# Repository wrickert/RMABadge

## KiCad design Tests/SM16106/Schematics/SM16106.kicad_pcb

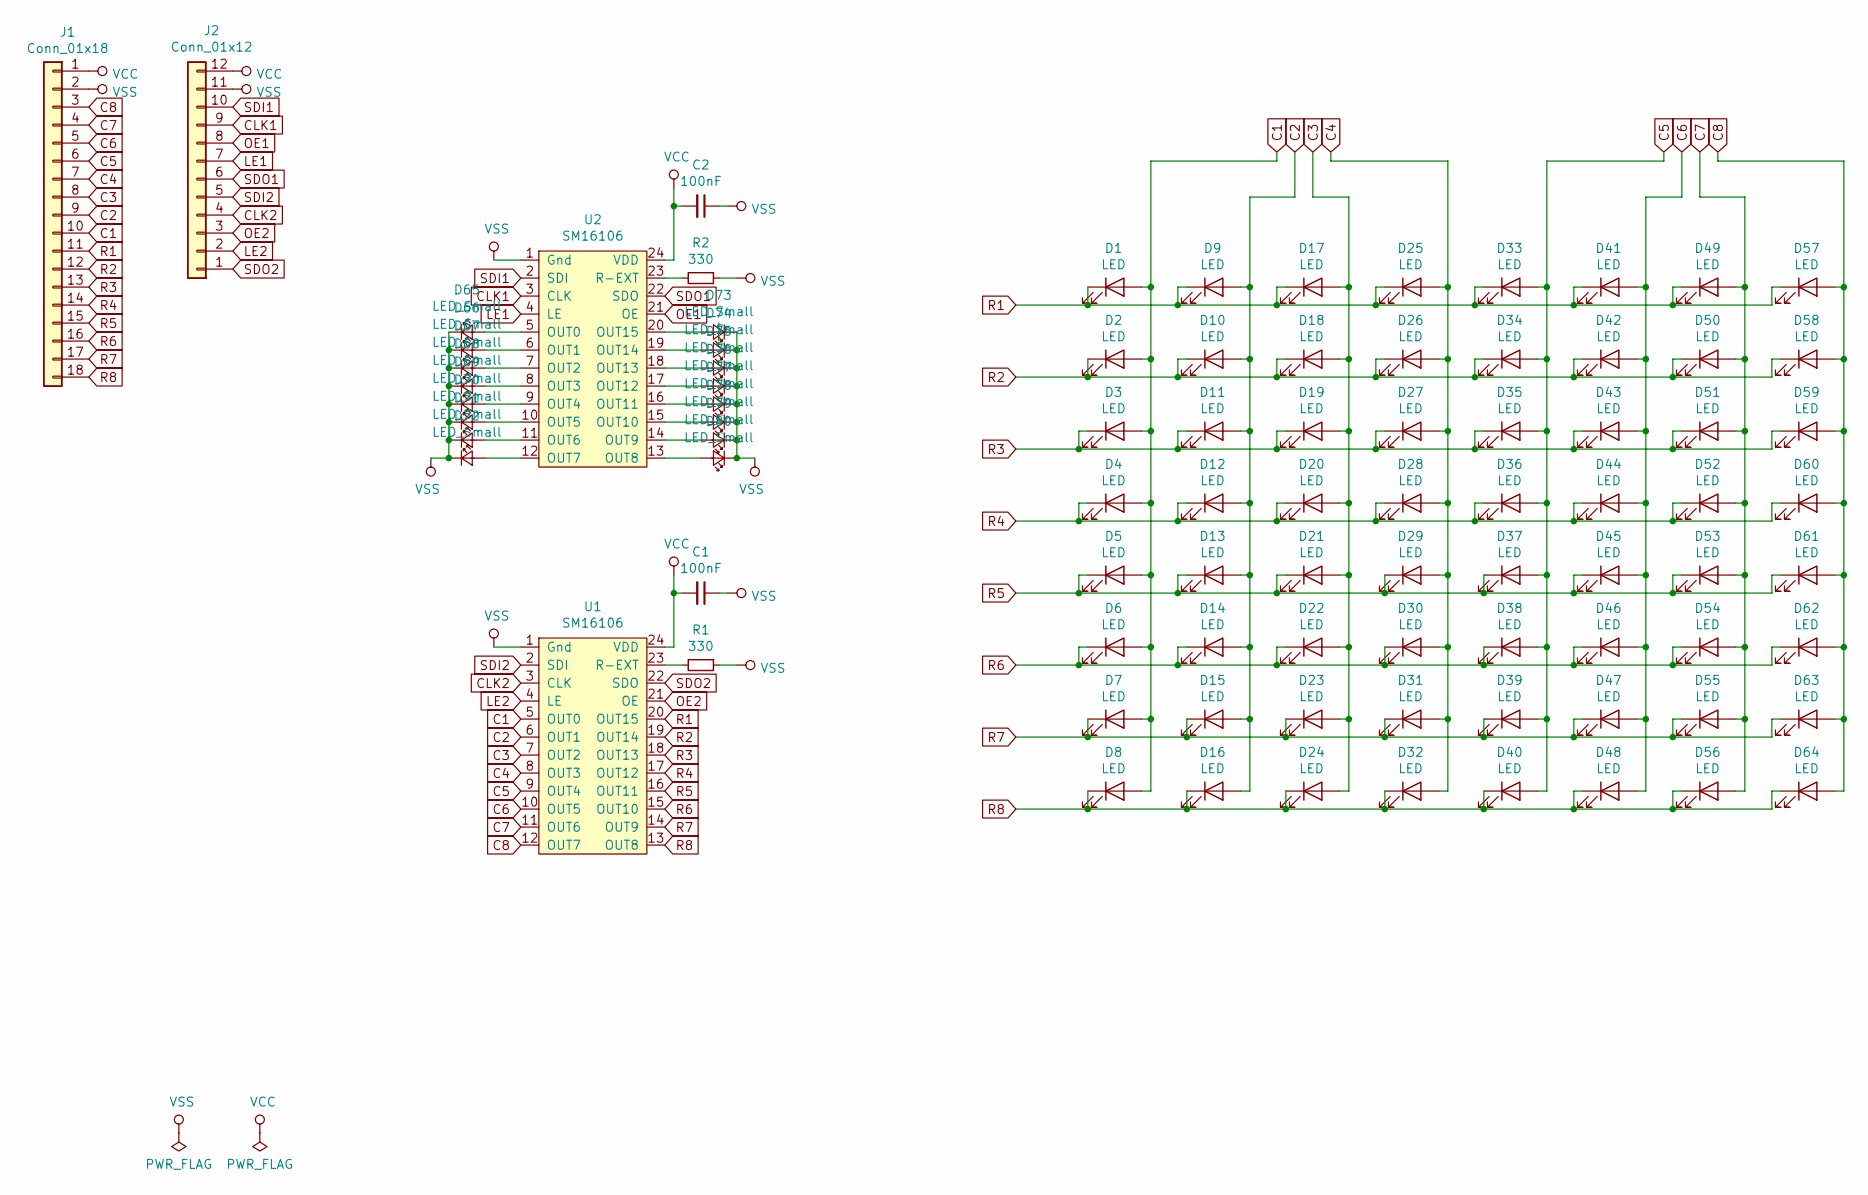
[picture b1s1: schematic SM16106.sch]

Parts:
C1, C2: 100nF; C_0805_2012Metric
D1, D2, D3, D4, D5, D6, D7, D8, D9, D10, D11, D12, D13, D14, D15, D16, D17, D18, D19, D20, D21, D22, D23, D24, D25, D26, D27, D28, D29, D30, D31, D32, D33, D34, D35, D36, D37, D38, D39, D40, D41, D42, D43, D44, D45, D46, D47, D48, D49, D50, D51, D52, D53, D54, D55, D56, D57, D58, D59, D60, D61, D62, D63, D64: LED; LED_0603_1608Metric
D65, D66, D67, D68, D69, D70, D71, D72, D73, D74, D75, D76, D77, D78, D79, D80: LED_Small; LED_0603_1608Metric
J1: Conn_01x18; PinHeader_1x18_P2.54mm_Vertical
J2: Conn_01x12; PinHeader_1x12_P2.54mm_Vertical
R1, R2: 330; R_0805_2012Metric
U1, U2: SM16106; QSOP-24_3.9x8.7mm_P0.635mm

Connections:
C1: D1.2 (A), D2.2 (A), D3.2 (A), D4.2 (A), D5.2 (A), D6.2 (A), D7.2 (A), D8.2 (A), J1.10, U1.5 (OUT0)
C2: D9.2 (A), D10.2 (A), D11.2 (A), D12.2 (A), D13.2 (A), D14.2 (A), D15.2 (A), D16.2 (A), J1.9, U1.6 (OUT1)
C3: D17.2 (A), D18.2 (A), D19.2 (A), D20.2 (A), D21.2 (A), D22.2 (A), D23.2 (A), D24.2 (A), J1.8, U1.7 (OUT2)
C4: D25.2 (A), D26.2 (A), D27.2 (A), D28.2 (A), D29.2 (A), D30.2 (A), D31.2 (A), D32.2 (A), J1.7, U1.8 (OUT3)
C5: D33.2 (A), D34.2 (A), D35.2 (A), D36.2 (A), D37.2 (A), D38.2 (A), D39.2 (A), D40.2 (A), J1.6, U1.9 (OUT4)
C6: D41.2 (A), D42.2 (A), D43.2 (A), D44.2 (A), D45.2 (A), D46.2 (A), D47.2 (A), D48.2 (A), J1.5, U1.10 (OUT5)
C7: D49.2 (A), D50.2 (A), D51.2 (A), D52.2 (A), D53.2 (A), D54.2 (A), D55.2 (A), D56.2 (A), J1.4, U1.11 (OUT6)
C8: D57.2 (A), D58.2 (A), D59.2 (A), D60.2 (A), D61.2 (A), D62.2 (A), D63.2 (A), D64.2 (A), J1.3, U1.12 (OUT7)
CLK1: J2.9, U2.3 (CLK)
CLK2: J2.4, U1.3 (CLK)
LE1: J2.7, U2.4 (LE)
LE2: J2.2, U1.4 (LE)
unnamed: D65.2 (A), U2.5 (OUT0)
unnamed: D66.2 (A), U2.6 (OUT1)
unnamed: D67.2 (A), U2.7 (OUT2)
unnamed: D68.2 (A), U2.8 (OUT3)
unnamed: D69.2 (A), U2.9 (OUT4)
unnamed: D70.2 (A), U2.10 (OUT5)
unnamed: D71.2 (A), U2.11 (OUT6)
unnamed: D72.2 (A), U2.12 (OUT7)
unnamed: D73.2 (A), U2.20 (OUT15)
unnamed: D74.2 (A), U2.19 (OUT14)
unnamed: D75.2 (A), U2.18 (OUT13)
unnamed: D76.2 (A), U2.17 (OUT12)
unnamed: D77.2 (A), U2.16 (OUT11)
unnamed: D78.2 (A), U2.15 (OUT10)
unnamed: D79.2 (A), U2.14 (OUT9)
unnamed: D80.2 (A), U2.13 (OUT8)
unnamed: R1.2, U1.23 (R-EXT)
unnamed: R2.2, U2.23 (R-EXT)
OE1: J2.8, U2.21 (OE)
OE2: J2.3, U1.21 (OE)
R1: D1.1 (K), D9.1 (K), D17.1 (K), D25.1 (K), D33.1 (K), D41.1 (K), D49.1 (K), D57.1 (K), J1.11, U1.20 (OUT15)
R2: D2.1 (K), D10.1 (K), D18.1 (K), D26.1 (K), D34.1 (K), D42.1 (K), D50.1 (K), D58.1 (K), J1.12, U1.19 (OUT14)
R3: D3.1 (K), D11.1 (K), D19.1 (K), D27.1 (K), D35.1 (K), D43.1 (K), D51.1 (K), D59.1 (K), J1.13, U1.18 (OUT13)
R4: D4.1 (K), D12.1 (K), D20.1 (K), D28.1 (K), D36.1 (K), D44.1 (K), D52.1 (K), D60.1 (K), J1.14, U1.17 (OUT12)
R5: D5.1 (K), D13.1 (K), D21.1 (K), D29.1 (K), D37.1 (K), D45.1 (K), D53.1 (K), D61.1 (K), J1.15, U1.16 (OUT11)
R6: D6.1 (K), D14.1 (K), D22.1 (K), D30.1 (K), D38.1 (K), D46.1 (K), D54.1 (K), D62.1 (K), J1.16, U1.15 (OUT10)
R7: D7.1 (K), D15.1 (K), D23.1 (K), D31.1 (K), D39.1 (K), D47.1 (K), D55.1 (K), D63.1 (K), J1.17, U1.14 (OUT9)
R8: D8.1 (K), D16.1 (K), D24.1 (K), D32.1 (K), D40.1 (K), D48.1 (K), D56.1 (K), D64.1 (K), J1.18, U1.13 (OUT8)
SDI1: J2.10, U2.2 (SDI)
SDI2: J2.5, U1.2 (SDI)
SDO1: J2.6, U2.22 (SDO)
SDO2: J2.1, U1.22 (SDO)
VCC: C1.2, C2.2, J1.1, J2.12, U1.24 (VDD), U2.24 (VDD)
VSS: C1.1, C2.1, D65.1 (K), D66.1 (K), D67.1 (K), D68.1 (K), D69.1 (K), D70.1 (K), D71.1 (K), D72.1 (K), D73.1 (K), D74.1 (K), D75.1 (K), D76.1 (K), D77.1 (K), D78.1 (K), D79.1 (K), D80.1 (K), J1.2, J2.11, R1.1, R2.1, U1.1 (Gnd), U2.1 (Gnd)

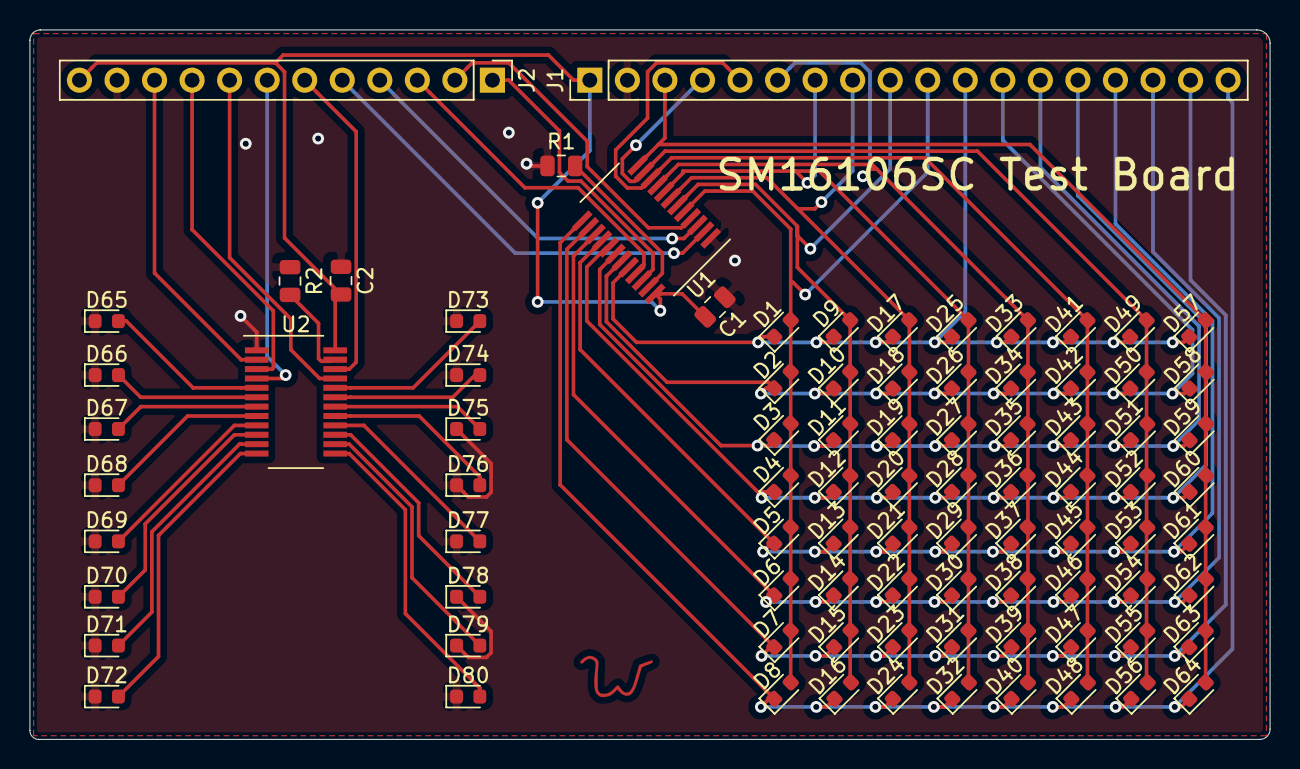
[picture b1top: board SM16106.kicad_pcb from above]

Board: 2 copper layers, 83.9 x 48.0 mm, 89 parts (0 on the bottom side), 46 nets.

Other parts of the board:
Ref**: Val**; W

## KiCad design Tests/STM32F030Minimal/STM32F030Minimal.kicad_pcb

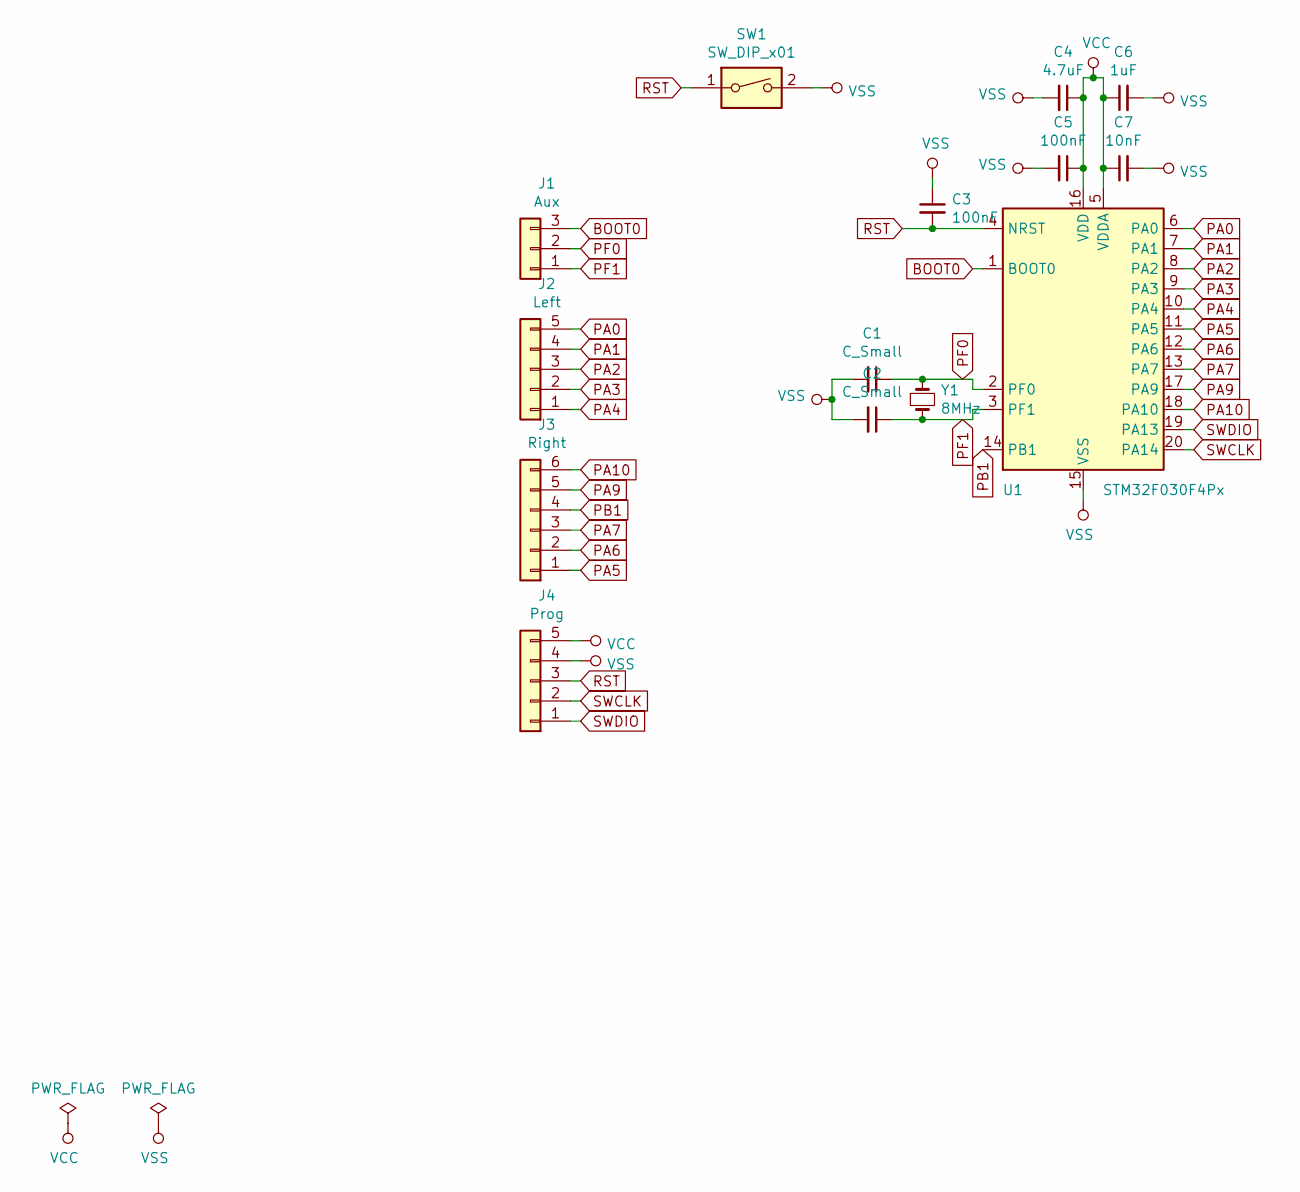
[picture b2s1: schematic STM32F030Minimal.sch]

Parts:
C1, C2: C_Small; C_0805_2012Metric
C3, C5: 100nF; C_0805_2012Metric
C4: 4.7uF; C_0805_2012Metric
C6: 1uF; C_0805_2012Metric
C7: 10nF; C_0805_2012Metric
J1: Aux; PinHeader_1x03_P2.54mm_Vertical
J2: Left; PinHeader_1x05_P2.54mm_Vertical
J3: Right; PinHeader_1x06_P2.54mm_Vertical
J4: Prog; PinHeader_1x05_P2.54mm_Vertical
SW1: SW_DIP_x01; SW_Push_1P1T_NO_CK_KSC7xxJ
U1: STM32F030F4Px; TSSOP-20_4.4x6.5mm_P0.65mm
Y1: 8MHz; Crystal_SMD_5032-2Pin_5.0x3.2mm

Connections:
BOOT0: J1.3, U1.1 (BOOT0)
PA0: J2.5, U1.6 (PA0)
PA1: J2.4, U1.7 (PA1)
PA2: J2.3, U1.8 (PA2)
PA3: J2.2, U1.9 (PA3)
PA4: J2.1, U1.10 (PA4)
PA5: J3.1, U1.11 (PA5)
PA6: J3.2, U1.12 (PA6)
PA7: J3.3, U1.13 (PA7)
PA9: J3.5, U1.17 (PA9)
PA10: J3.6, U1.18 (PA10)
PB1: J3.4, U1.14 (PB1)
PF0: C1.1, J1.2, U1.2 (PF0), Y1.1
PF1: C2.1, J1.1, U1.3 (PF1), Y1.2
RST: C3.2, J4.3, SW1.1, U1.4 (NRST); also elsewhere on the board
SWCLK: J4.2, U1.20 (PA14)
SWDIO: J4.1, U1.19 (PA13)
VCC: C4.1, C5.1, C6.1, C7.1, J4.5, U1.5 (VDDA), U1.16 (VDD)
VSS: C1.2, C2.2, C3.1, C4.2, C5.2, C6.2, C7.2, J4.4, SW1.2, U1.15 (VSS); also elsewhere on the board

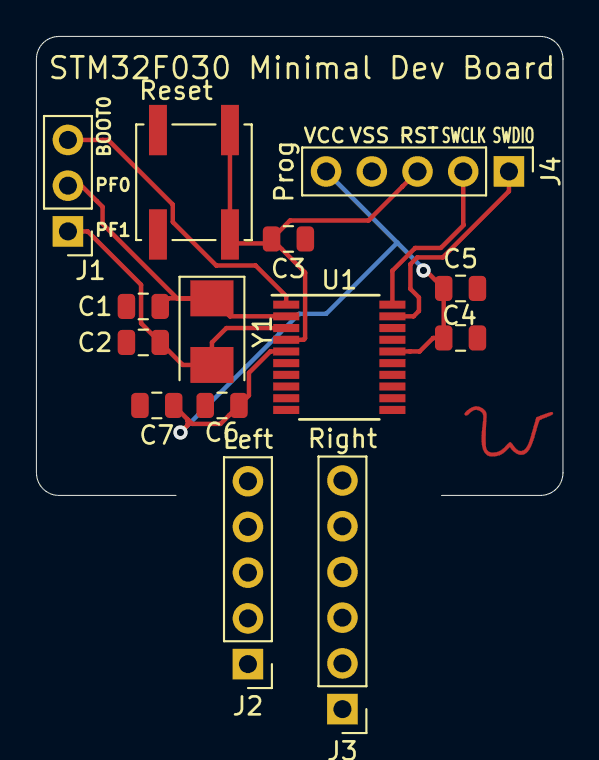
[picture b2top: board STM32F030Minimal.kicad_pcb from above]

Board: 2 copper layers, 29.2 x 25.5 mm, 15 parts (0 on the bottom side), 19 nets.

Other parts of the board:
Ref**: Val**; W
Reset: SW_DIP_x01; SW_Push_1P1T_NO_CK_KSC7xxJ

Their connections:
RST: Reset.1; also elsewhere on the board
VSS: Reset.2; also elsewhere on the board

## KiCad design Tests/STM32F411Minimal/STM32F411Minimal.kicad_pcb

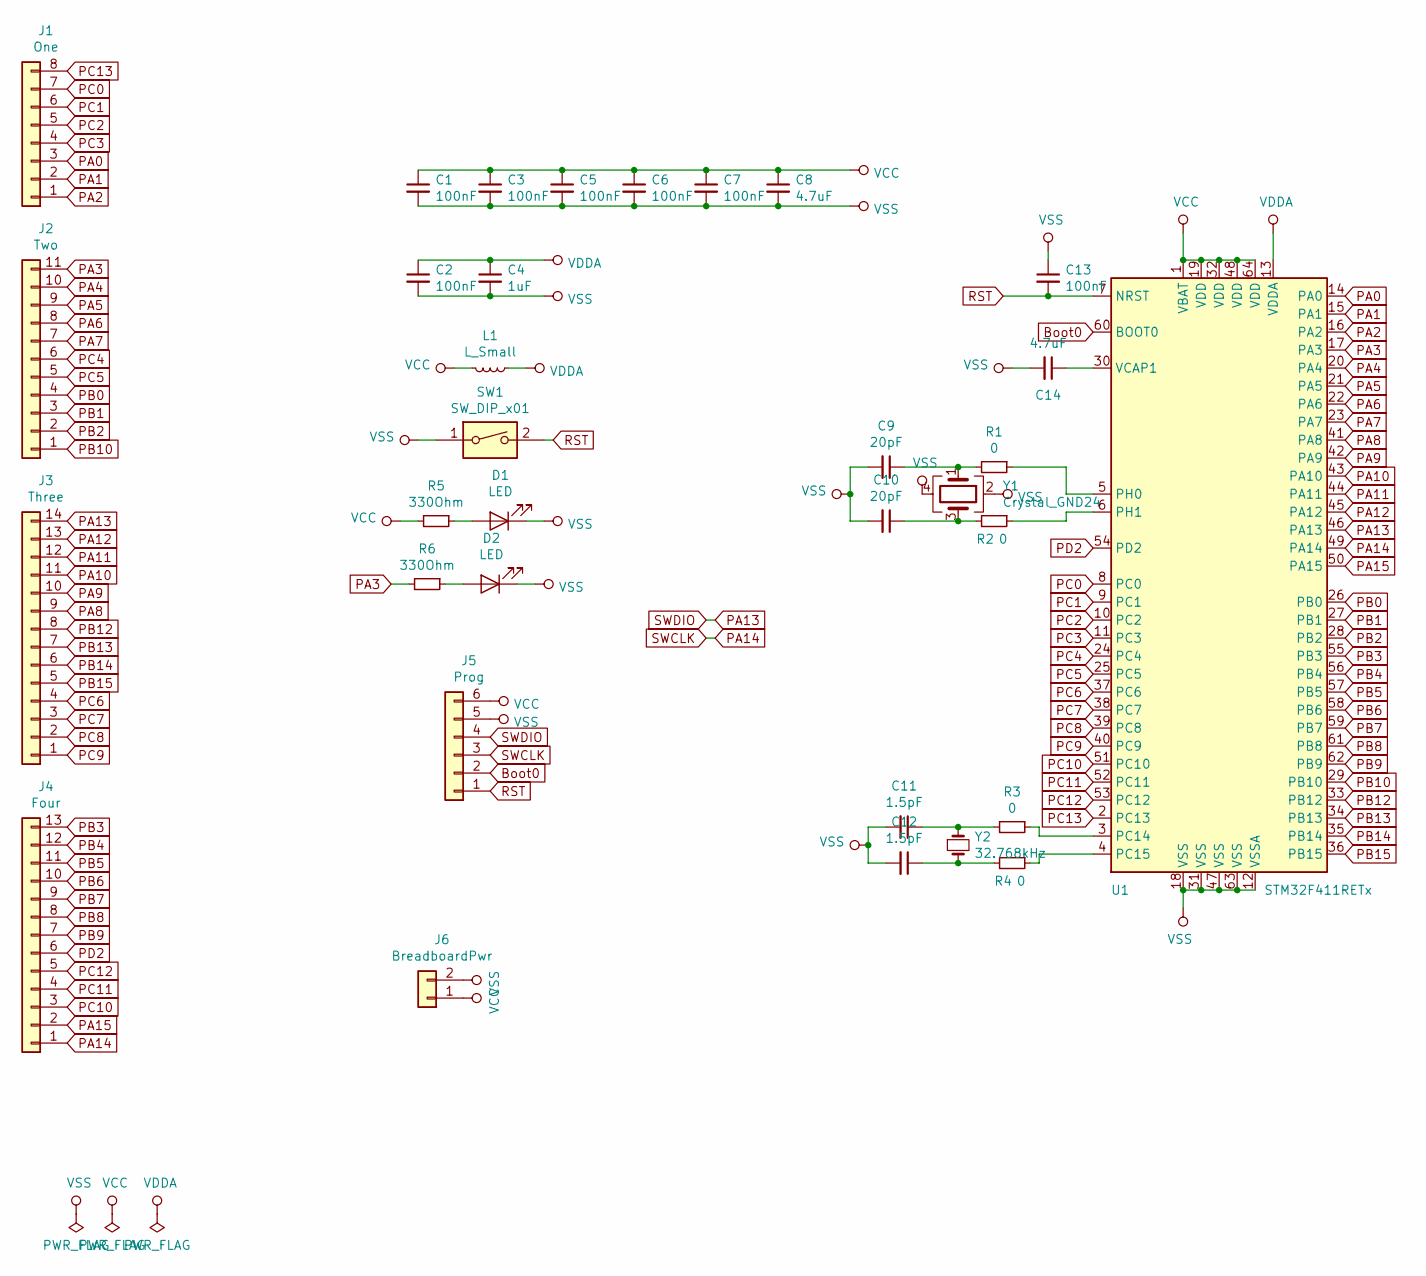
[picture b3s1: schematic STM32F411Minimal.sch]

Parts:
C1, C2, C3, C5, C6, C7, C13: 100nF; C_0805_2012Metric
C4: 1uF; C_0805_2012Metric
C8, C14: 4.7uF; C_0805_2012Metric
C9, C10: 20pF; C_0805_2012Metric
C11, C12: 1.5pF; C_0805_2012Metric
D1, D2: LED; LED_0603_1608Metric
J1: One; PinHeader_1x08_P2.54mm_Vertical
J2: Two; PinHeader_1x11_P2.54mm_Vertical
J3: Three; PinHeader_1x14_P2.54mm_Vertical
J4: Four; PinHeader_1x13_P2.54mm_Vertical
J5: Prog; PinHeader_1x06_P2.54mm_Vertical
J6: BreadboardPwr; PinHeader_1x02_P2.54mm_Vertical
L1: L_Small; L_0603_1608Metric
R1, R2, R3, R4: 0; R_0805_2012Metric
R5, R6: 330Ohm; R_0805_2012Metric
SW1: SW_DIP_x01; SW_Push_1P1T_NO_CK_KSC7xxJ
U1: STM32F411RETx; LQFP-64_10x10mm_P0.5mm
Y1: Crystal_GND24; Crystal_SMD_SeikoEpson_TSX3225-4Pin_3.2x2.5mm
Y2: 32.768kHz; Crystal_SMD_3215-2Pin_3.2x1.5mm

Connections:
Boot0: J5.2, U1.60 (BOOT0)
unnamed: C9.1, R1.2, Y1.1
unnamed: C10.1, R2.2, Y1.3
unnamed: C11.1, R3.2, Y2.1
unnamed: C12.1, R4.2, Y2.2
unnamed: C14.1, U1.30 (VCAP1)
unnamed: D1.2 (A), R5.1
unnamed: D2.2 (A), R6.1
unnamed: R1.1, U1.5 (PH0)
unnamed: R2.1, U1.6 (PH1)
unnamed: R3.1, U1.3 (PC14)
unnamed: R4.1, U1.4 (PC15)
PA0: J1.3, U1.14 (PA0)
PA1: J1.2, U1.15 (PA1)
PA2: J1.1, U1.16 (PA2)
PA3: J2.11, R6.2, U1.17 (PA3)
PA4: J2.10, U1.20 (PA4)
PA5: J2.9, U1.21 (PA5)
PA6: J2.8, U1.22 (PA6)
PA7: J2.7, U1.23 (PA7)
PA8: J3.9, U1.41 (PA8)
PA9: J3.10, U1.42 (PA9)
PA10: J3.11, U1.43 (PA10)
PA11: J3.12, U1.44 (PA11)
PA12: J3.13, U1.45 (PA12)
PA13: J3.14, J5.4, U1.46 (PA13)
PA14: J4.1, J5.3, U1.49 (PA14)
PA15: J4.2, U1.50 (PA15)
PB0: J2.4, U1.26 (PB0)
PB1: J2.3, U1.27 (PB1)
PB2: J2.2, U1.28 (PB2)
PB3: J4.13, U1.55 (PB3)
PB4: J4.12, U1.56 (PB4)
PB5: J4.11, U1.57 (PB5)
PB6: J4.10, U1.58 (PB6)
PB7: J4.9, U1.59 (PB7)
PB8: J4.8, U1.61 (PB8)
PB9: J4.7, U1.62 (PB9)
PB10: J2.1, U1.29 (PB10)
PB12: J3.8, U1.33 (PB12)
PB13: J3.7, U1.34 (PB13)
PB14: J3.6, U1.35 (PB14)
PB15: J3.5, U1.36 (PB15)
PC0: J1.7, U1.8 (PC0)
PC1: J1.6, U1.9 (PC1)
PC2: J1.5, U1.10 (PC2)
PC3: J1.4, U1.11 (PC3)
PC4: J2.6, U1.24 (PC4)
PC5: J2.5, U1.25 (PC5)
PC6: J3.4, U1.37 (PC6)
PC7: J3.3, U1.38 (PC7)
PC8: J3.2, U1.39 (PC8)
PC9: J3.1, U1.40 (PC9)
PC10: J4.3, U1.51 (PC10)
PC11: J4.4, U1.52 (PC11)
PC12: J4.5, U1.53 (PC12)
PC13: J1.8, U1.2 (PC13)
PD2: J4.6, U1.54 (PD2)
RST: C13.2, J5.1, SW1.2, U1.7 (NRST)
VCC: C1.1, C3.1, C5.1, C6.1, C7.1, C8.1, J5.6, J6.1, L1.2, R5.2, U1.1 (VBAT), U1.19 (VDD), U1.32 (VDD), U1.48 (VDD), U1.64 (VDD)
VDDA: C2.1, C4.1, L1.1, U1.13 (VDDA)
VSS: C1.2, C2.2, C3.2, C4.2, C5.2, C6.2, C7.2, C8.2, C9.2, C10.2, C11.2, C12.2, C13.1, C14.2, D1.1 (K), D2.1 (K), J5.5, J6.2, SW1.1, U1.12 (VSSA), U1.18 (VSS), U1.31 (VSS), U1.47 (VSS), U1.63 (VSS), Y1.2, Y1.4

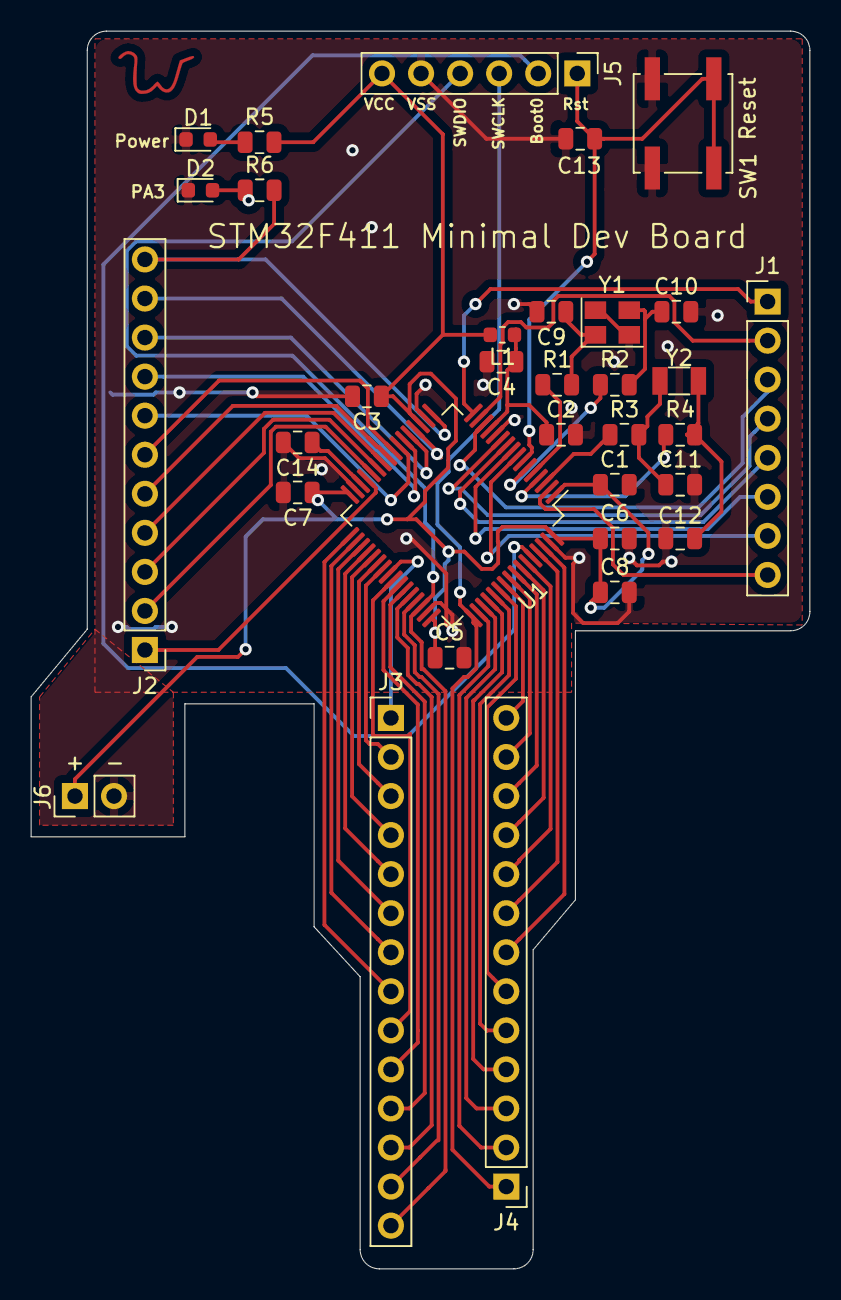
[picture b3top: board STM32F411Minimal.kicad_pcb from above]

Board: 2 copper layers, 50.7 x 80.5 mm, 34 parts (0 on the bottom side), 62 nets.

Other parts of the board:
Ref**: Val**; W

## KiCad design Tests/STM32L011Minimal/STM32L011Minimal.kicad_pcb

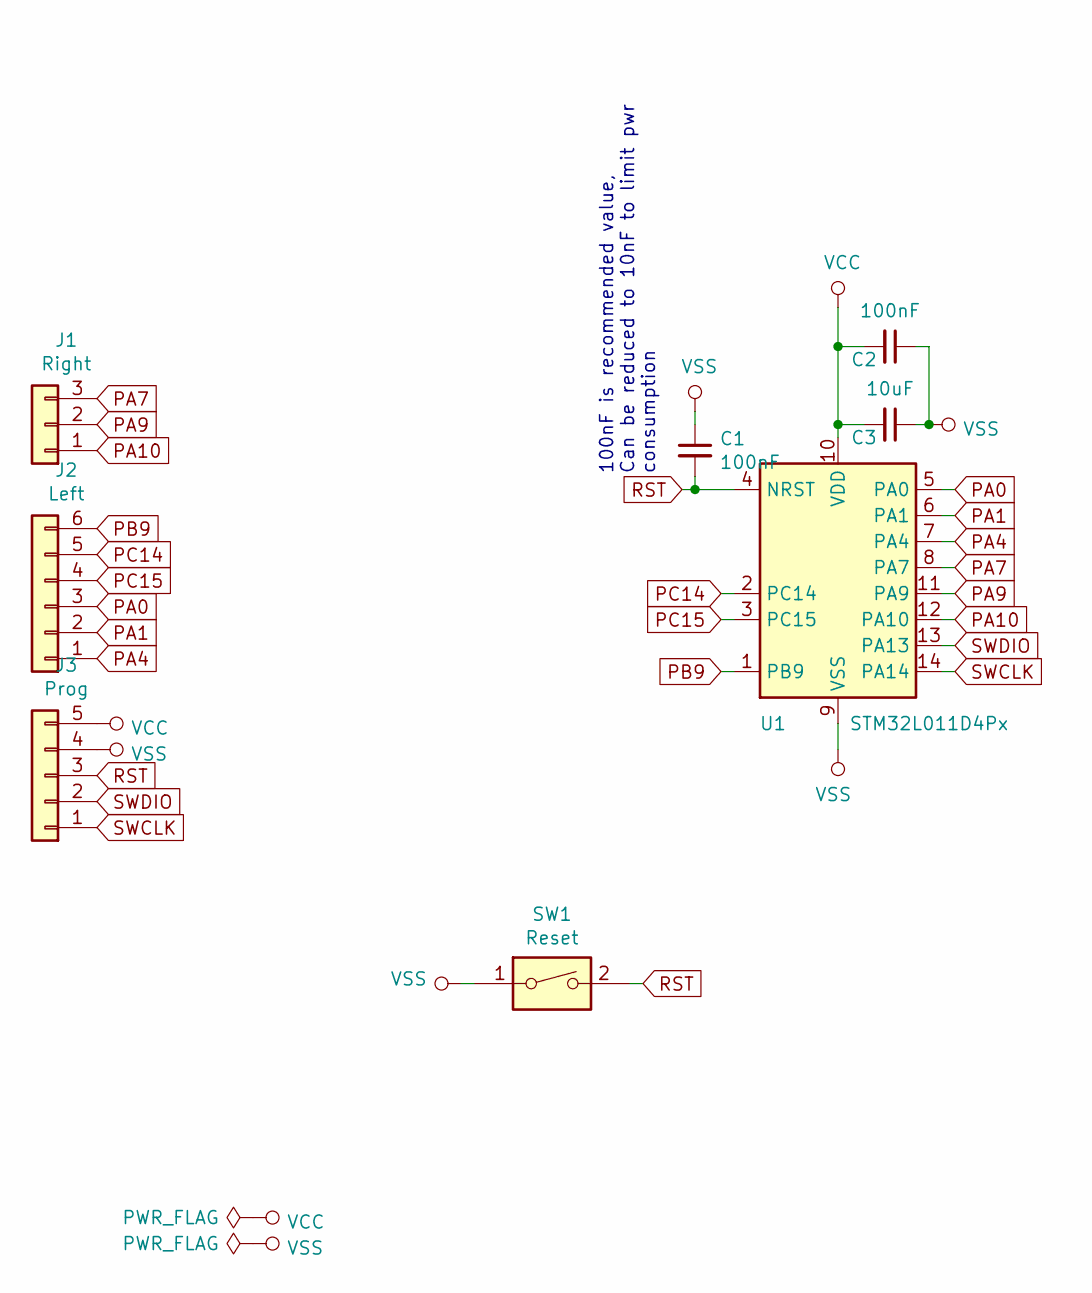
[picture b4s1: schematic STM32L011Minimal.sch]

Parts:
C1, C2: 100nF; C_0805_2012Metric
C3: 10uF; C_0805_2012Metric
J1: Right; PinHeader_1x03_P2.54mm_Vertical
J2: Left; PinHeader_1x06_P2.54mm_Vertical
J3: Prog; PinHeader_1x05_P2.54mm_Vertical
SW1: Reset; SW_Push_1P1T_NO_CK_KSC7xxJ
U1: STM32L011D4Px; TSSOP-14_4.4x5mm_P0.65mm

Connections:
PA0: J2.3, U1.5 (PA0)
PA1: J2.2, U1.6 (PA1)
PA4: J2.1, U1.7 (PA4)
PA7: J1.3, U1.8 (PA7)
PA9: J1.2, U1.11 (PA9)
PA10: J1.1, U1.12 (PA10)
PB9: J2.6, U1.1 (PB9)
PC14: J2.5, U1.2 (PC14)
PC15: J2.4, U1.3 (PC15)
RST: C1.2, J3.3, SW1.2, U1.4 (NRST)
SWCLK: J3.1, U1.14 (PA14)
SWDIO: J3.2, U1.13 (PA13)
VCC: C2.2, C3.2, J3.5, U1.10 (VDD)
VSS: C1.1, C2.1, C3.1, J3.4, SW1.1, U1.9 (VSS)

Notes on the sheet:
100nF is recommended value, Can be reduced to 10nF to limit pwr consumption

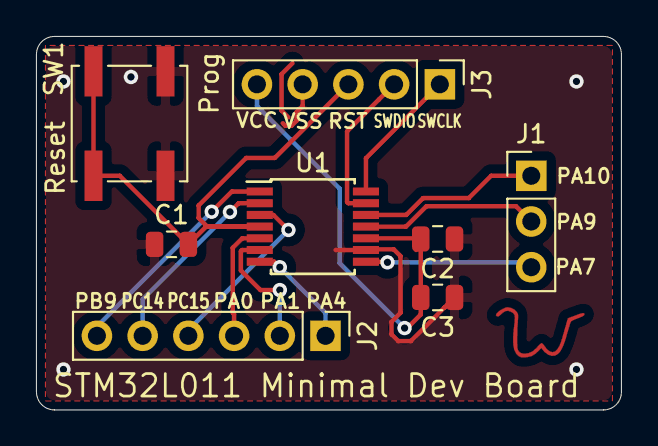
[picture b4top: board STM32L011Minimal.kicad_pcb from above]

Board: 2 copper layers, 32.5 x 20.8 mm, 9 parts (0 on the bottom side), 14 nets.

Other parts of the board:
Ref**: Val**; W

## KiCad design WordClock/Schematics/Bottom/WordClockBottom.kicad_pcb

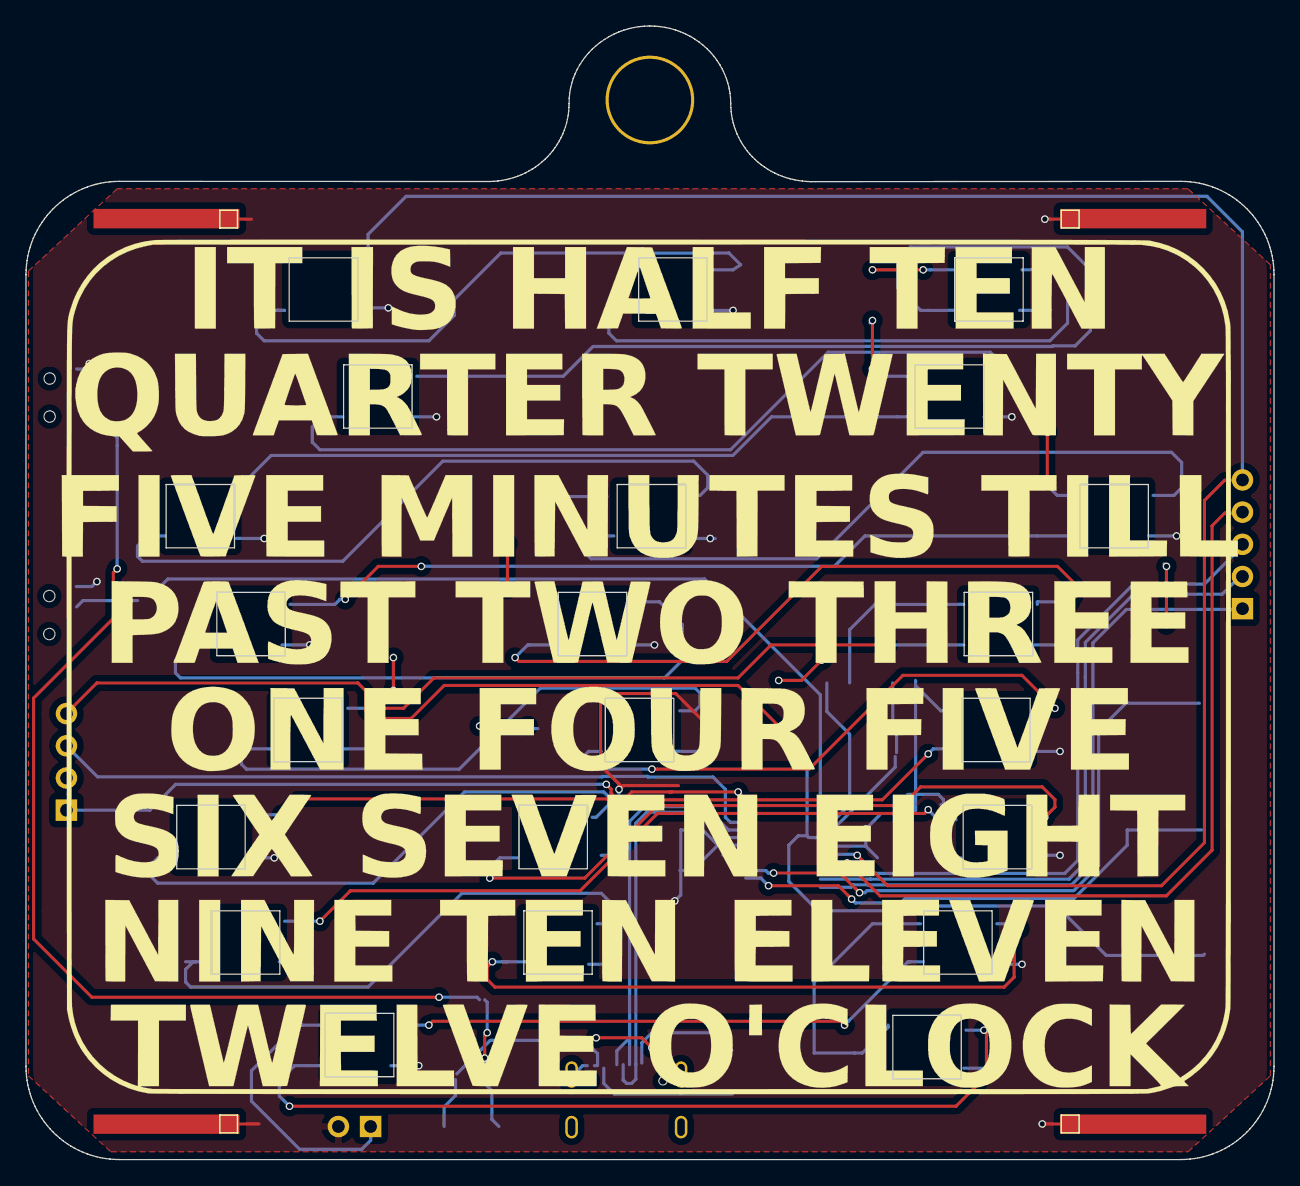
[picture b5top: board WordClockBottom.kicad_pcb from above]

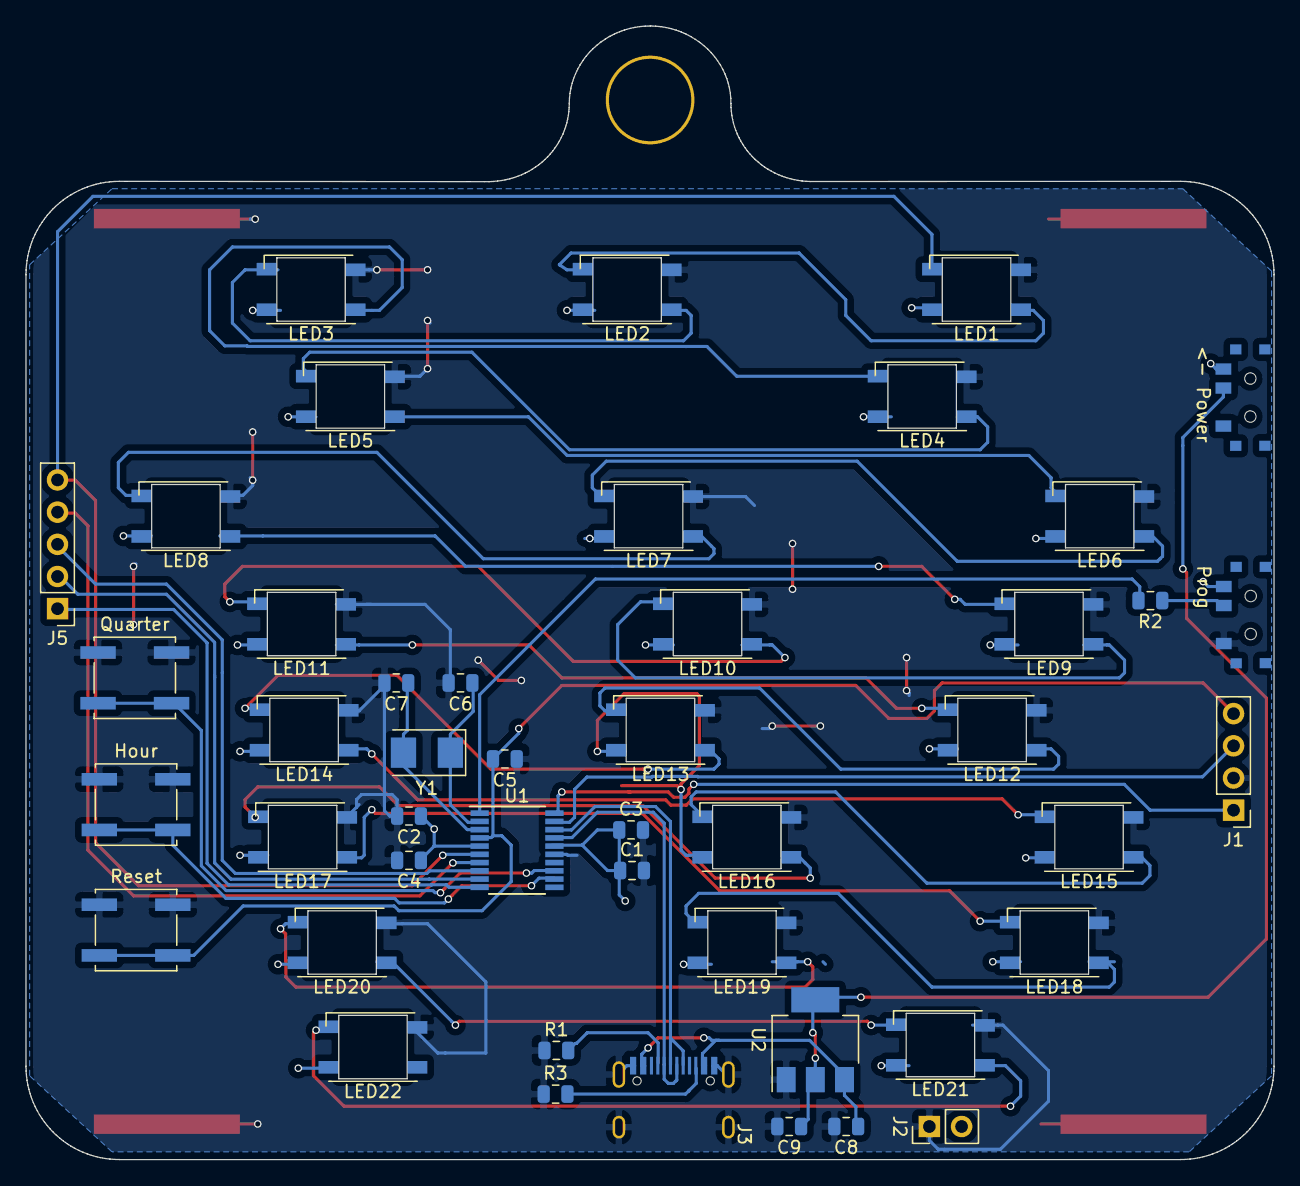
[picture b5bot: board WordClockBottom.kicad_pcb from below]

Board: 2 copper layers, 98.5 x 89.5 mm, 46 parts (46 on the bottom side), 43 nets.

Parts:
<- Power: Power; SK-3296S_switch
C1: 4.7uF; C_0805_2012Metric
C2, C8, C9: 1uF; C_0805_2012Metric
C3, C5: 100nF; C_0805_2012Metric
C4: 10nF; C_0805_2012Metric
C6, C7: 20pF; C_0805_2012Metric
Hour: Hour; SW_Push_1P1T_NO_CK_KSC6xxJ
J1: Prog; PinHeader_1x04_P2.54mm_Vertical
J2: Conn_01x02; PinHeader_1x02_P2.54mm_Vertical
J3: USB_C_Receptacle; USB_C_Receptical-Jing
J5: Left; PinHeader_1x05_P2.54mm_Vertical
LED1, LED2, LED3, LED4, LED5, LED6, LED7, LED8, LED9, LED10, LED11, LED12, LED13, LED14, LED15, LED16, LED17, LED18, LED19, LED20, LED21, LED22: WS2812B; WS2812B-Sunken
Prog: Prog; SK-3296S_switch
Quarter: Quarter; SW_Push_1P1T_NO_CK_KSC6xxJ
R1, R2, R3: 10k; R_0805_2012Metric
Reset: Reset; SW_Push_1P1T_NO_CK_KSC6xxJ
U1: STM32F042F6Px; TSSOP-20_4.4x6.5mm_P0.65mm
U2: TLV1117-33; SOT-223-3_TabPin2
Y1: 8MHz; Crystal_SMD_5032-2Pin_5.0x3.2mm

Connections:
+5V: J3.A4, J3.A9, J3.B4, J3.B9, U2.3
BOOT0: R2.2, U1.1
D+: J3.A6, J3.B6, U1.18
D-: J3.A7, J3.B7, U1.17
Dout1: LED10.2, LED11.4
Dout2: LED20.2, LED21.4
unnamed: <- Power.2, C9.1, U2.2
unnamed: J3.A5, R1.2
unnamed: J3.B5, R3.2
unnamed: LED1.2, LED2.4
unnamed: LED2.2, LED3.4
unnamed: LED3.2, LED4.4
unnamed: LED4.2, LED5.4
unnamed: LED5.2, LED6.4
unnamed: LED6.2, LED7.4
unnamed: LED7.2, LED8.4
unnamed: LED8.2, LED9.4
unnamed: LED9.2, LED10.4
unnamed: LED11.2, LED12.4
unnamed: LED12.2, LED13.4
unnamed: LED13.2, LED14.4
unnamed: LED14.2, LED15.4
unnamed: LED15.2, LED16.4
unnamed: LED16.2, LED17.4
unnamed: LED17.2, LED18.4
unnamed: LED18.2, LED19.4
unnamed: LED19.2, LED20.4
unnamed: LED21.2, LED22.4
unnamed: Prog.2, R2.1
PA0: J5.5, LED1.4, U1.6
PA1: J5.4, U1.7
PA2: J5.3, U1.8
PA3: J5.2, U1.9
PA4: J5.1, U1.10
PA6: Hour.1, U1.12
PA7: Quarter.1, U1.13
PF0: C6.1, U1.2, Y1.1
PF1: C7.1, U1.3, Y1.2
RST: C5.2, J1.4, Reset.1, U1.4
SWCLK: J1.1, U1.20
SWDIO: J1.3, U1.19
VCC: <- Power.1, C1.1, C2.1, C3.1, C4.1, J2.2, LED1.1, LED2.1, LED3.1, LED4.1, LED5.1, LED6.1, LED7.1, LED8.1, LED9.1, LED10.1, LED11.1, LED12.1, LED13.1, LED14.1, LED15.1, LED16.1, LED17.1, LED18.1, LED19.1, LED20.1, LED21.1, LED22.1, Prog.1, U1.5, U1.16
VSS: C1.2, C2.2, C3.2, C4.2, C5.1, C6.2, C7.2, C8.2, C9.2, Hour.2, J1.2, J2.1, J3.A1, J3.A12, J3.B1, J3.B12, J3.S1, LED1.3, LED2.3, LED3.3, LED4.3, LED5.3, LED6.3, LED7.3, LED8.3, LED9.3, LED10.3, LED11.3, LED12.3, LED13.3, LED14.3, LED15.3, LED16.3, LED17.3, LED18.3, LED19.3, LED20.3, LED21.3, LED22.3, Prog.3, Quarter.2, R1.1, R3.1, Reset.2, U1.15, U2.1

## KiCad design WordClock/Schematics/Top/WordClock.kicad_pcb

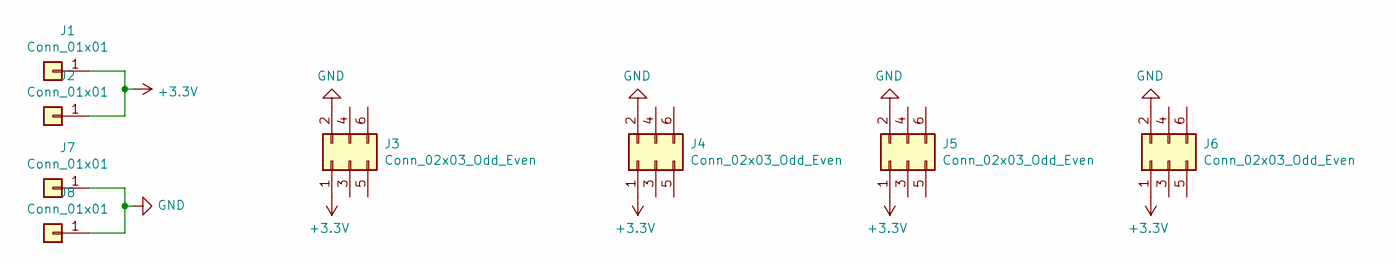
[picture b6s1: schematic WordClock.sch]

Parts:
J1, J2, J7, J8: Conn_01x01; TestPoint_Pad_1.0x1.0mm
J3, J4, J5, J6: Conn_02x03_Odd_Even; PinSocket_2x03_P2.54mm_Vertical

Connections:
+3V3: J1.1, J2.1, J3.1, J4.1, J5.1, J6.1
GND: J3.2, J4.2, J5.2, J6.2, J7.1, J8.1
